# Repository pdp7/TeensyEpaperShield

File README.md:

# TeensyEpaperShield
Teensy shield designed by [Jarek Lupinski](https://hackaday.io/Jarek) to connect e-paper display from [Pervasive Displays](http://www.pervasivedisplays.com/products#iTC):
 > The Simplest Way To Start Playing With A Fascinating New Low-Power Screen!

## OSH Park Shared Project
* [Teensy e-Paper shield](https://oshpark.com/shared_projects/3KynIVn6)

## Blog posts
* [Teensy E-Paper shield](https://blog.oshpark.com/2016/08/27/teensy-e-paper-shield/)
* [Teensy E-Paper shield update](https://blog.oshpark.com/2016/09/07/teensy-e-paper-shield-update/)

## Hackaday.io project
* [Teensy E-Paper Adapter Board](https://hackaday.io/project/13327-teensy-e-paper-adapter-board)

## Design files
* [EpaperTeensyBoard.sch](https://cdn.hackaday.io/files/13327570182368/EpaperTeensyBoard.sch)
* [EpaperTeensyBoard.brd](https://cdn.hackaday.io/files/13327570182368/EpaperTeensyBoard.brd)

## Images
* [images dir](/images)

## Video
* [YouTube: Teensy E-Paper Shield](https://www.youtube.com/watch?v=xAe1GGP35UQ)

## Bill of Materials
* [Teensy 3.x](https://oshpark.com/teensy) or [Teensy LC](http://store.oshpark.com/products/teensy-lc)
* [Pervasive Displays 2.15" e-paper with ITC (E2215CS062)](http://www.digikey.com/product-detail/en/pervasive-displays/E2215CS062/E2215CS062-ND/5975949)
* [Hirose Electric Co Ltd FH34SRJ-34S-0.5SH FPC connector]( https://www.digikey.com/short/3hv1q0 )
* [Parts list exported from EAGLE](https://cdn.hackaday.io/files/13327570182368/EpaperTeensyBoardPartlist.txt)
* [Digi-Key shopping cart #1](http://www.digikey.com/short/3mhnrd)
* [Digi-Key shopping cart #2](http://www.digikey.com/short/3m9wq3)

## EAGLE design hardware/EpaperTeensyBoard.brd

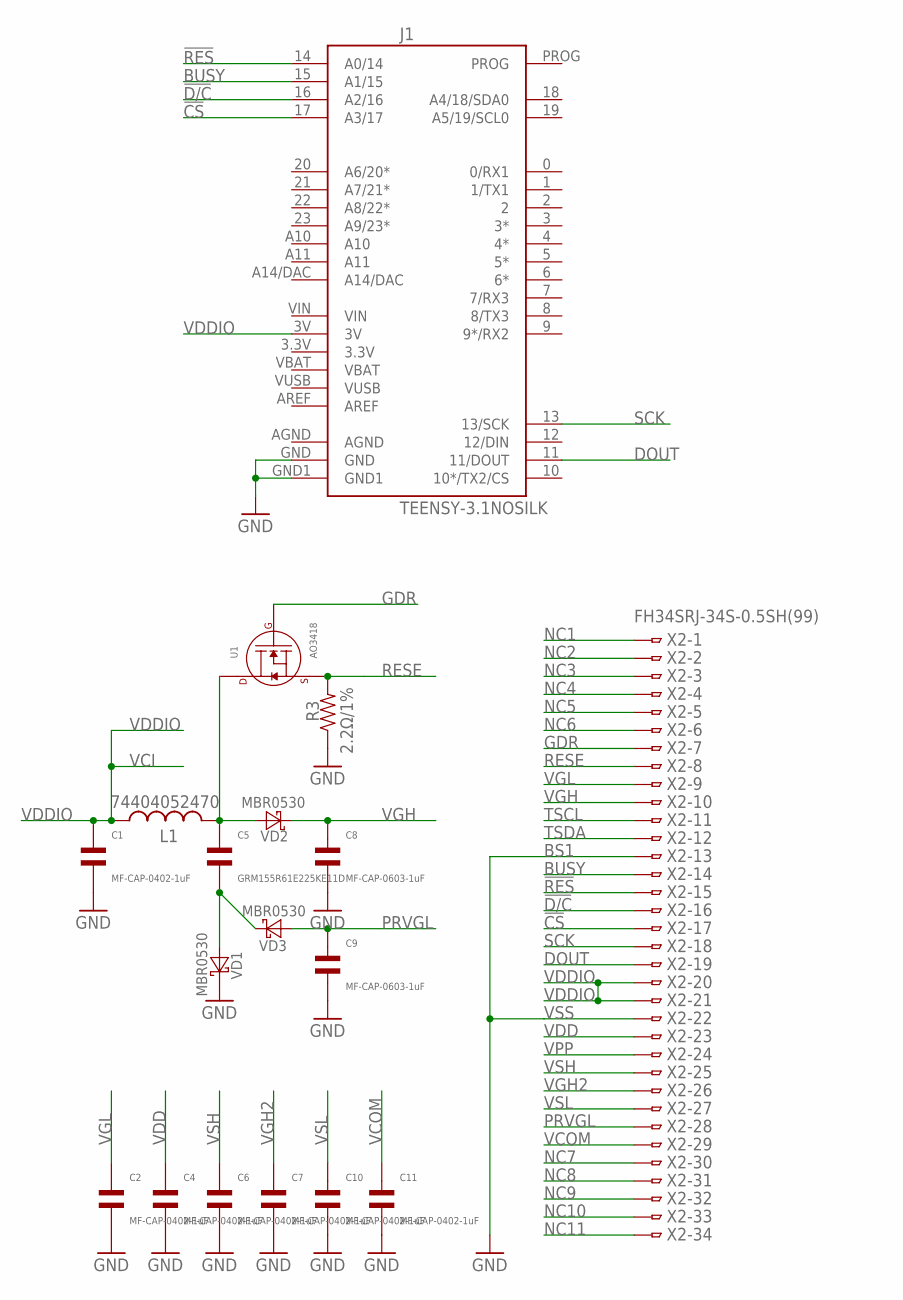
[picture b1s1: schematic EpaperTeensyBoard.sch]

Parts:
C1, C2, C4, C6, C7, C10, C11: MF-CAP-0402-1uF; C0805
C5: GRM155R61E225KE11D; C0805
C8, C9: MF-CAP-0603-1uF; C0805
J1: TEENSY-3.1NOSILK; TEENSY-3.1_NOSILK
L1: 74404052470; POWER-CHOKE_WE-TPC
R3: 2.2Ω/1%; R0805
U1: AO3418; SOT-23-3
VD1, VD2, VD3: MBR0530; SOD123
X2: FH34SRJ-34S-0.5SH(99); FH12-34S-0.5SH

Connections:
!CS: J1.17 (A3/17), X2.17
!D/C: J1.16 (A2/16), X2.16
!RES: J1.14 (A0/14), X2.15
BUSY: J1.15 (A1/15), X2.14
DOUT: J1.11 (11/DOUT), X2.19
GDR: U1.P$1 (GATE), X2.7
GND: C1.P$2, C2.P$2, C4.P$2, C6.P$2, C7.P$2, C8.P$2, C9.P$2, C10.P$2, C11.P$2, J1.GND, J1.GND1, R3.P$1, VD1.C, X2.13, X2.22
unnamed: C5.P$1, L1.2, U1.P$3 (DRAIN), VD2.A
unnamed: C5.P$2, VD1.A, VD3.C
NC1: X2.1
NC2: X2.2
NC3: X2.3
NC4: X2.4
NC5: X2.5
NC6: X2.6
NC7: X2.30
NC8: X2.31
NC9: X2.32
NC10: X2.33
NC11: X2.34
PRVGL: C9.P$1, VD3.A, X2.28
RESE: R3.P$2, U1.P$2 (SOURCE), X2.8
SCK: J1.13 (13/SCK), X2.18
TSCL: X2.11
TSDA: X2.12
VCOM: C11.P$1, X2.29
VDD: C4.P$1, X2.23
VDDIO: C1.P$1, J1.3V, L1.1, X2.20, X2.21
VGH: C8.P$1, VD2.C, X2.10
VGH2: C7.P$1, X2.26
VGL: C2.P$1, X2.9
VPP: X2.24
VSH: C6.P$1, X2.25
VSL: C10.P$1, X2.27

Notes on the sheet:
BS1
VSS
VCI

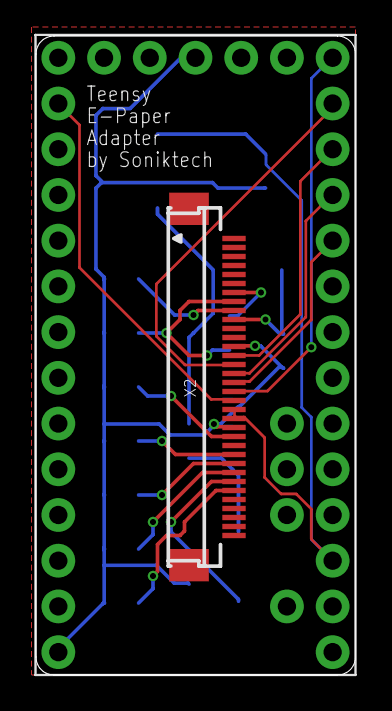
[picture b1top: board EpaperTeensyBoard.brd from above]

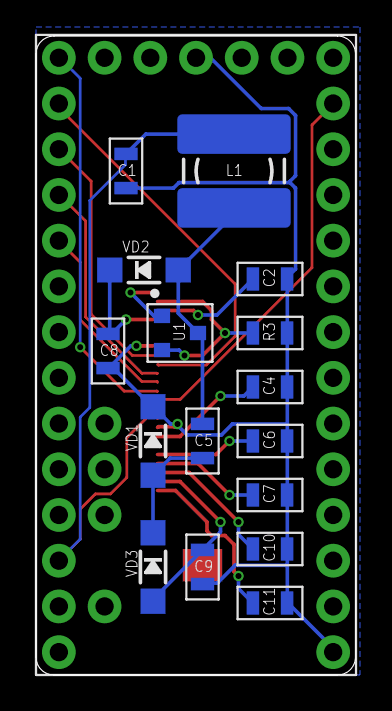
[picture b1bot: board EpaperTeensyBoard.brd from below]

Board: 2 copper layers, 17.8 x 35.5 mm, 18 parts (17 on the bottom side), 20 nets.

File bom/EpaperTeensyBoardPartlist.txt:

Partlist

Exported from EpaperTeensyBoard.sch at 9/10/2016 6:15 PM

EAGLE Version 7.5.0 Copyright (c) 1988-2015 CadSoft

Assembly variant: 

Part     Value                 Device                 Package            Library                   Sheet

C1       1uF                   CAPACITOR_NP_0805      C0805              MF_Passives               1
C2       1uF                   CAPACITOR_NP_0805      C0805              MF_Passives               1
C4       1uF                   CAPACITOR_NP_0805      C0805              MF_Passives               1
C5       1uF                   CAPACITOR_NP_0805      C0805              MF_Passives               1
C6       1uF                   CAPACITOR_NP_0805      C0805              MF_Passives               1
C7       1uF                   CAPACITOR_NP_0805      C0805              MF_Passives               1
C8       1uF                   CAPACITOR_NP_0805      C0805              MF_Passives               1
C9       1uF                   CAPACITOR_NP_0805      C0805              MF_Passives               1
C10      1uF                   CAPACITOR_NP_0805      C0805              MF_Passives               1
C11      1uF                   CAPACITOR_NP_0805      C0805              MF_Passives               1
J1       TEENSY-3.1NOSILK      TEENSY-3.1NOSILK       TEENSY-3.1_NOSILK  SparkFun-Boards           1
L1       74404052470           L-USWE-TPC             POWER-CHOKE_WE-TPC rcl                       1
R3       2.2?/1%               RESISTOR_0805          R0805              MF_Passives               1
U1       AO3418                N-CHANNEL_FET_SOT-23-3 SOT-23-3           MF_Discrete_Semiconductor 1
VD1      MBR0530               DIODE-SCHOTTKY-SOD123  SOD123             diode                     1
VD2      MBR0530               DIODE-SCHOTTKY-SOD123  SOD123             diode                     1
VD3      MBR0530               DIODE-SCHOTTKY-SOD123  SOD123             diode                     1
X2       FH34SRJ-34S-0.5SH(99) FH12-34S-0.5SH         FH12-34S-0.5SH     con-hirose                1

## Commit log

2016-09-10 Add demo code from Jarek on Hackaday.io
    Demo for Teensy E-Paper Adapter Board by jarek319:
    https://hackaday.io/project/13327-teensy-e-paper-adapter-board
2016-09-10 Add messages for Portland Mini Maker Faire 2016
2016-09-16 add parts list
2016-09-19 Rename project
2016-09-19 renamed sketch
2016-09-19 add note about authorship
2016-09-19 move into firmware dir
2016-09-19 Add EAGLE schematic and layout
    EAGLE design files by Jarek Lupinksi on Hackaday.io:
    https://hackaday.io/project/13327/files
2016-09-19 add image of assembled board and osh park pcb preview
2016-09-19 add images
2016-09-19 add BoM info
2016-09-19 update BoM image

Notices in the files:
parts and their libraries:
SparkFun-Boards: Licensing: Creative Commons ShareAlike 4.0 International - https://creativecommons.org/licenses/by-sa/4.0
